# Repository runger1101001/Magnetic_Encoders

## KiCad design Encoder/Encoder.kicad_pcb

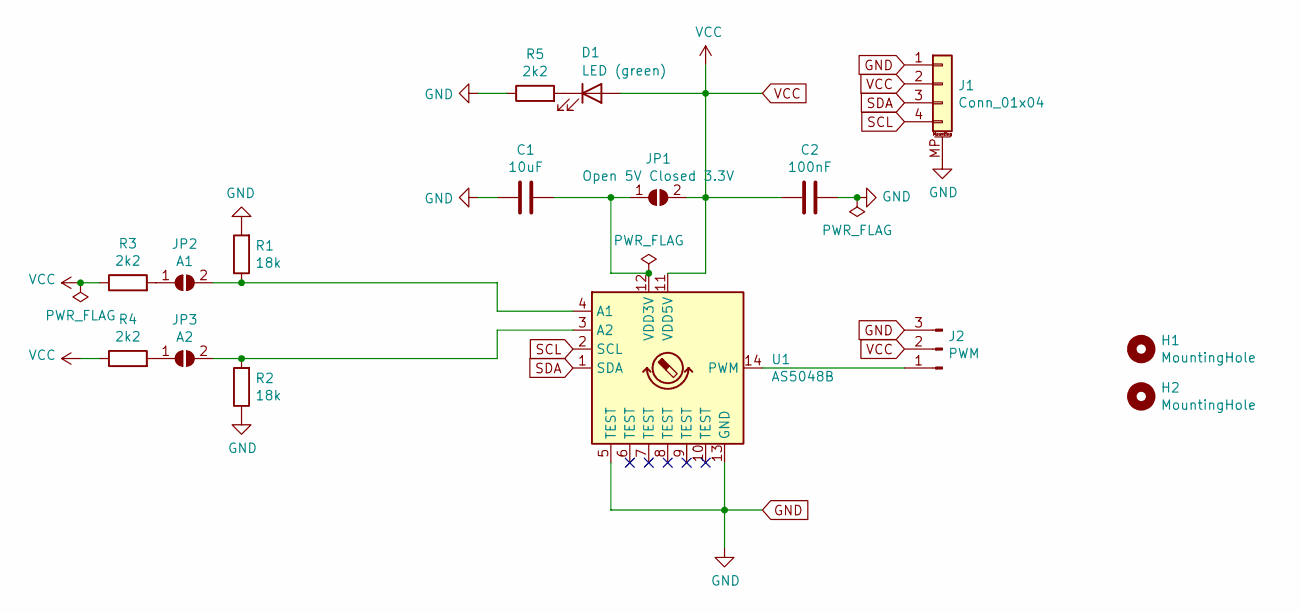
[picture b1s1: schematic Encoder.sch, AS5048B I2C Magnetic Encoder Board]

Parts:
C1: 10uF; C_0402_1005Metric; Part GRM155R60J106ME15D
C2: 100nF; C_0402_1005Metric; Part 04026D104KAT2A
D1: LED (green); LED_0402_1005Metric; Part 150040VS73240
H1, H2: MountingHole; MountingHole_2.2mm_M2
J1: Conn_01x04; JST_SH_SM04B-SRSS-TB_1x04-1MP_P1.00mm_Horizontal; Manufacturer Part # SH_SM04B-SRSS-TB
J2: PWM; PinHeader_1x03_P2.54mm_Vertical
JP1: Open 5V Closed 3.3V; SolderJumper-2_P1.3mm_Open_TrianglePad1.0x1.5mm
JP2: A1; SolderJumper-2_P1.3mm_Open_TrianglePad1.0x1.5mm
JP3: A2; SolderJumper-2_P1.3mm_Open_TrianglePad1.0x1.5mm
R1, R2: 18k; R_0402_1005Metric
R3, R4, R5: 2k2; R_0402_1005Metric; Part Generic
U1: AS5048B; TSSOP-14_4.4x5mm_P0.65mm; Part AS5048B

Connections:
GND: C1.2, C2.1, J1.1, J1.MP (MountPin), J2.3, R1.2, R2.1, R5.1, U1.5 (TEST), U1.13 (GND)
unnamed: C1.1, JP1.1 (A), U1.12 (VDD3V)
unnamed: D1.1 (K), R5.2
unnamed: J2.1, U1.14 (PWM)
unnamed: JP2.1 (A), R3.2
unnamed: JP2.2 (B), R1.1, U1.4 (A1)
unnamed: JP3.1 (A), R4.2
unnamed: JP3.2 (B), R2.2, U1.3 (A2)
SCL: J1.4, U1.2 (SCL)
SDA: J1.3, U1.1 (SDA)
VCC: C2.2, D1.2 (A), J1.2, J2.2, JP1.2 (B), R3.1, R4.1, U1.11 (VDD5V)

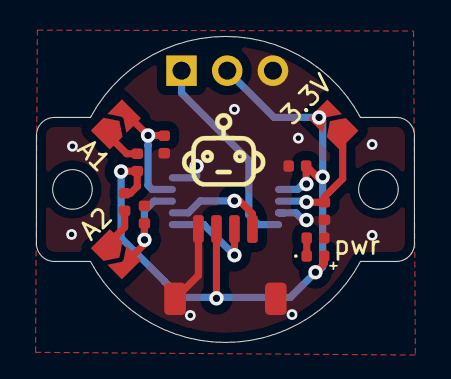
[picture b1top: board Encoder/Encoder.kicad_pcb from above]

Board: 2 copper layers, 21.0 x 17.0 mm, 16 parts (1 on the bottom side), 11 nets.

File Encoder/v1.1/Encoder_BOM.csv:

Item #,Ref Des,Qty,Manufacturer,Mfg Part #, Description / Value,Package,Type,Your Instructions / Notes
1,C1,1,Generic,Generic,10µF 6.3V Ceramic,0402,SMD,Generic
2,C2,1,Generic,Generic,100nF 6.3V Ceramic,0402,SMD,Generic
3,D1,1,Generic,e.g.: SML-P13PT,LED Green (λ 560nm)  Vf 2.1V @20mA,0402,SMD,"Generic, e.g. https://eu.mouser.com/datasheet/2/348/sml-p1-e-1874493.pdf"
4,J1,1,JST,SM04B-SRSS-TB,Conn_01x04,SM04B-SRSS-TB,SMD,http://www.jst-mfg.com/product/pdf/eng/eSH.pdf?5f7229e446c85
5,"R1,R2",2,Generic,Generic,18kΩ 1/16W 2%,0402,SMD,Generic
6,"R3,R4,R5",3,Generic,Generic,2.2kΩ 1/16W 2%,0402,SMD,Generic
7,U1,1,AMS,AS5048B,AS5048B,TSSOP-14,SMD,https://ams.com/documents/20143/36005/AS5048_DS000298_4-00.pdf

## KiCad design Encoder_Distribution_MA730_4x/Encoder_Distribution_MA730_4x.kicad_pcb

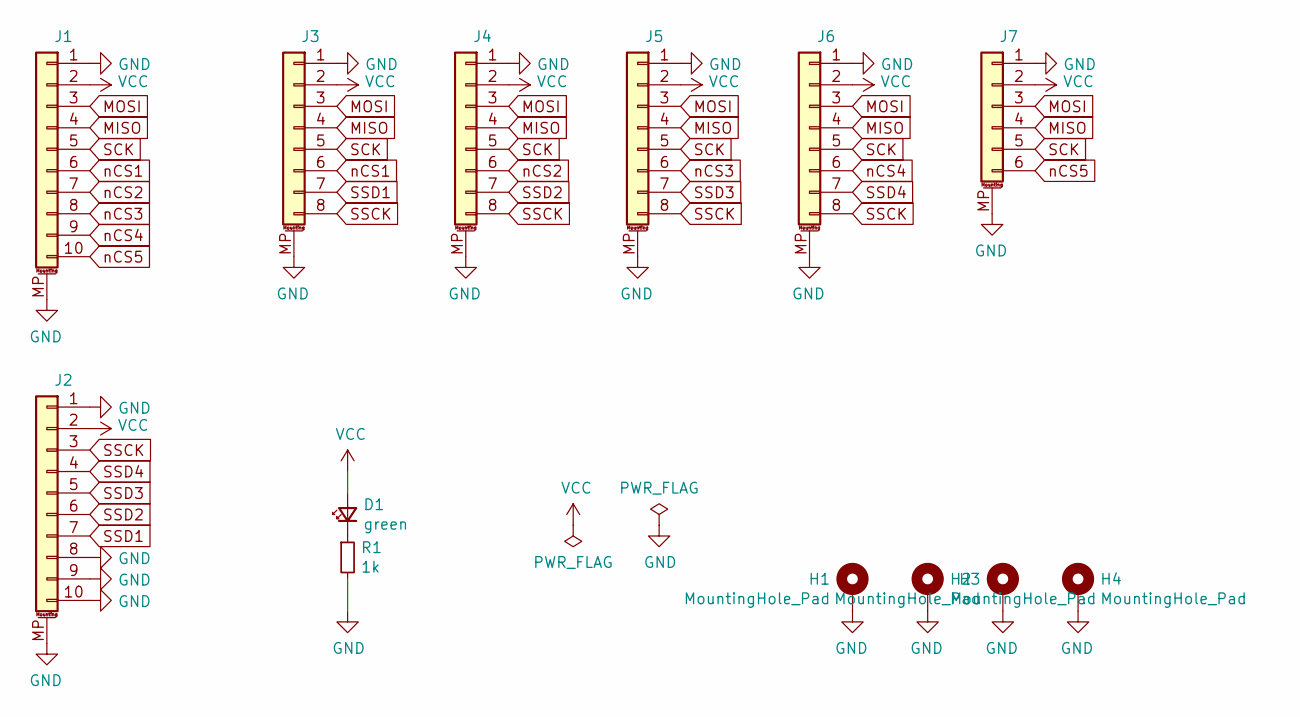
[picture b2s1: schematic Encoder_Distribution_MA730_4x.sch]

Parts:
D1: green; LED_0402_1005Metric; Part 150040VS73240
H1, H2, H3, H4: MountingHole_Pad; MountingHole_2.2mm_M2_ISO7380_Pad
J1, J2: Conn_01x10_MountingPin; JST_SH_SM10B-SRSS-TB_1x10-1MP_P1.00mm_Horizontal; Part SH_SM10B-SRSS-TB_1x10
J3, J4, J5, J6: Conn_01x08_MountingPin; JST_SH_BM08B-SRSS-TB_1x08-1MP_P1.00mm_Vertical; Part SH_BM06B-SRSS-TB_1x08
J7: Conn_01x06_MountingPin; JST_SH_BM06B-SRSS-TB_1x06-1MP_P1.00mm_Vertical; Part SH_BM06B-SRSS-TB_1x06
R1: 1k; R_0402_1005Metric

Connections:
GND: H1.1, H2.1, H3.1, H4.1, J1.1, J1.MP (MountPin), J2.1, J2.8, J2.9, J2.10, J2.MP (MountPin), J3.1, J3.MP (MountPin), J4.1, J4.MP (MountPin), J5.1, J5.MP (MountPin), J6.1, J6.MP (MountPin), J7.1, J7.MP (MountPin), R1.2
MISO: J1.4, J3.4, J4.4, J5.4, J6.4, J7.4
MOSI: J1.3, J3.3, J4.3, J5.3, J6.3, J7.3
unnamed: D1.1 (K), R1.1
SCK: J1.5, J3.5, J4.5, J5.5, J6.5, J7.5
SSCK: J2.3, J3.8, J4.8, J5.8, J6.8
SSD1: J2.7, J3.7
SSD2: J2.6, J4.7
SSD3: J2.5, J5.7
SSD4: J2.4, J6.7
VCC: D1.2 (A), J1.2, J2.2, J3.2, J4.2, J5.2, J6.2, J7.2
nCS1: J1.6, J3.6
nCS2: J1.7, J4.6
nCS3: J1.8, J5.6
nCS4: J1.9, J6.6
nCS5: J1.10, J7.6

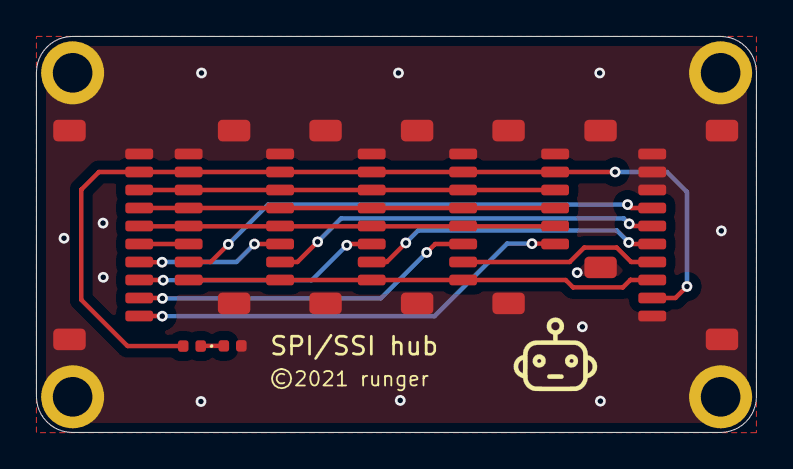
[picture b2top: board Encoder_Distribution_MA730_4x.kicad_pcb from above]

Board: 2 copper layers, 40.0 x 22.0 mm, 13 parts (0 on the bottom side), 16 nets.

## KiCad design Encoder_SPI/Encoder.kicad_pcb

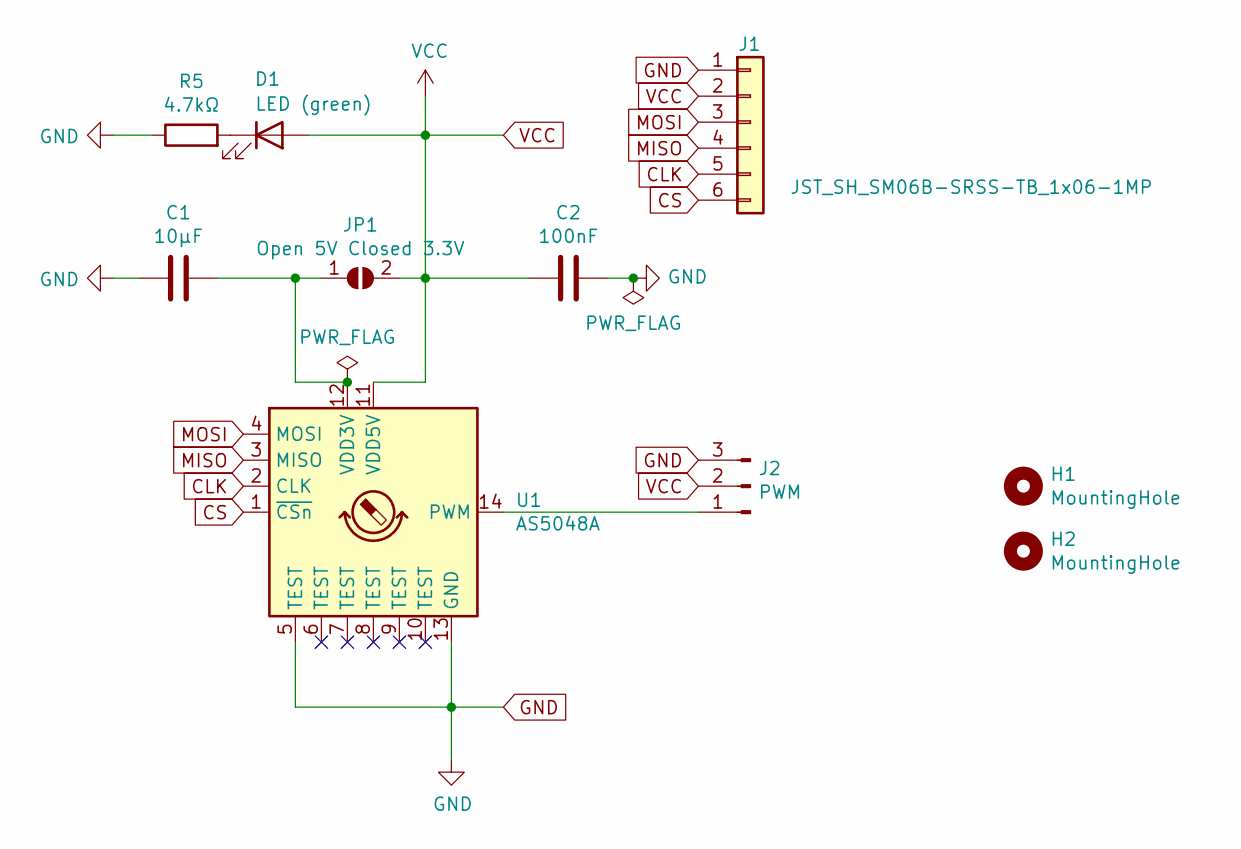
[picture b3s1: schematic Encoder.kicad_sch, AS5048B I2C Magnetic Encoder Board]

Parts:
C1: 10µF; C_0402_1005Metric
C2: 100nF; C_0402_1005Metric
D1: LED (green); LED_0402_1005Metric
H1, H2: MountingHole; MountingHole_2.2mm_M2
J1: JST_SH_SM06B-SRSS-TB_1x06-1MP; JST_SH_SM06B-SRSS-TB_1x06-1MP_P1.00mm_Horizontal; Manufacturer Part # JST_SH_SM06B-SRSS-TB_1x06-1MP
J2: PWM; PinHeader_1x03_P2.54mm_Vertical
JP1: Open 5V Closed 3.3V; SolderJumper-2_P1.3mm_Bridged_RoundedPad1.0x1.5mm
R5: 4.7kΩ; R_0402_1005Metric
U1: AS5048A; TSSOP-14_4.4x5mm_P0.65mm; Part AS5048A

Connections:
CLK: J1.5, U1.2 (CLK)
CS: J1.6, U1.1 (~CSn)
GND: C1.2, C2.1, J1.1, J2.3, R5.1, U1.5 (TEST), U1.13 (GND)
MISO: J1.4, U1.3 (MISO)
MOSI: J1.3, U1.4 (MOSI)
unnamed: C1.1, JP1.1 (A), U1.12 (VDD3V)
unnamed: D1.1 (K), R5.2
unnamed: J2.1, U1.14 (PWM)
VCC: C2.2, D1.2 (A), J1.2, J2.2, JP1.2 (B), U1.11 (VDD5V)

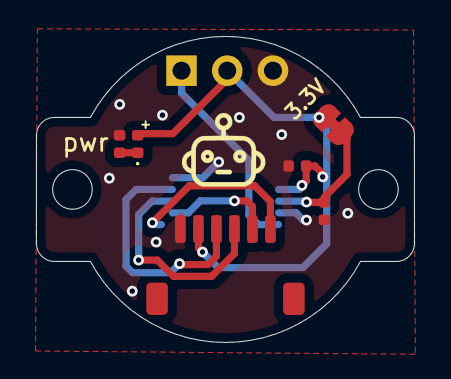
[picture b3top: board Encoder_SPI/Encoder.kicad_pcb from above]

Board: 2 copper layers, 21.0 x 17.0 mm, 10 parts (1 on the bottom side), 9 nets.

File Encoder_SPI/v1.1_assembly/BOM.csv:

Item #,Ref Des,Qty,Manufacturer,Mfg Part #, Description / Value,Package,Type,Your Instructions / Notes
1,U1,1,AMS,AS5048A,AS5048A,TSSOP-14_4.4x5mm_P0.65mm,SMD,
2,J1,1,JST,JST_SH_SM06B-SRSS-TB_1x06-1MP,JST SH 1.0mm 6-pin horizontal socket,JST_SH_SM06B-SRSS-TB_1x06-1MP_P1.00mm_Horizontal,SMD,
7,R5,1,Generic,Generic,4k7,R_0402_1005Metric,SMD,
8,D1,1,ROHM,SML-P12MTT86,Green LED,LED_0402_1005Metric,SMD,"Please choose inexpensive green LED, for example ROHM SML-P13FTT86R"
9,C2,1,Samsung,CL05B104KQ5NNNC,100nF 6.3V Ceramic,C_0402_1005Metric,SMD,
10,C1,1,Murata,ZRB15XR61A106ME01D,10uF 10V Ceramic,C_0402_1005Metric,SMD,

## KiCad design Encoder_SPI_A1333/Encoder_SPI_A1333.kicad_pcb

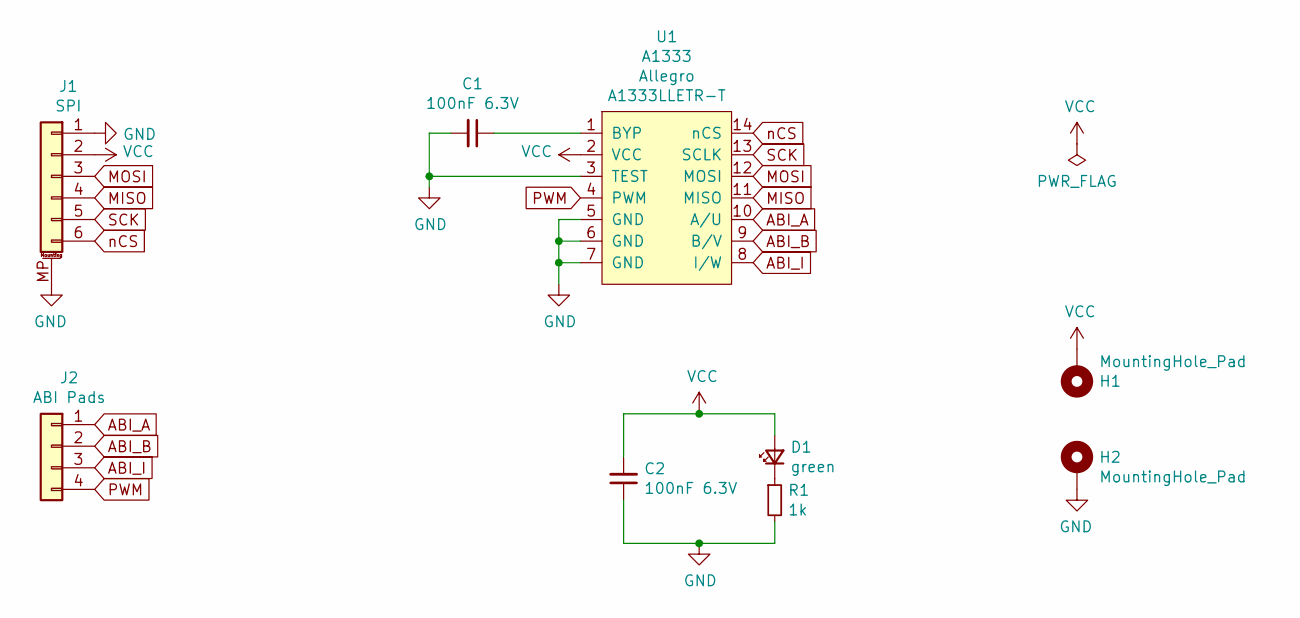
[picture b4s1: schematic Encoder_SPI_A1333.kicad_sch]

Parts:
C1, C2: 100nF 6.3V; C_0402_1005Metric; Part Generic
D1: green; LED_0402_1005Metric; Part 150040VS73240
H1, H2: MountingHole_Pad; MountingHole_2.2mm_M2_ISO7380_Pad
J1: Conn_01x06_MountingPin; JST_SH_SM06B-SRSS-TB_1x06-1MP_P1.00mm_Horizontal; Part SH_SM06B-SRSS-TB_1x06-1MP_P1.00mm_Horiz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
J2: Castellations_ABI; PinHeader_1x04_P2.54mm_Vertical
R1: 1k; R_0402_1005Metric; Part Generic 1k Resistor
U1: A1333; TSSOP-14_4.4x5mm_P0.65mm; Part A1333LLETR-T

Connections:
ABI_A: J2.1, U1.10 (A/U)
ABI_B: J2.2, U1.9 (B/V)
ABI_I: J2.3, U1.8 (I/W)
GND: C1.2, C2.1, H2.1, J1.1, J1.MP (MountPin), R1.2, U1.3 (TEST), U1.5 (GND), U1.6 (GND), U1.7 (GND)
MISO: J1.4, U1.11 (MISO)
MOSI: J1.3, U1.12 (MOSI)
unnamed: C1.1, U1.1 (BYP)
unnamed: D1.1 (K), R1.1
PWM: J2.4, U1.4 (PWM)
SCK: J1.5, U1.13 (SCLK)
VCC: C2.2, D1.2 (A), H1.1, J1.2, U1.2 (VCC)
nCS: J1.6, U1.14 (nCS)

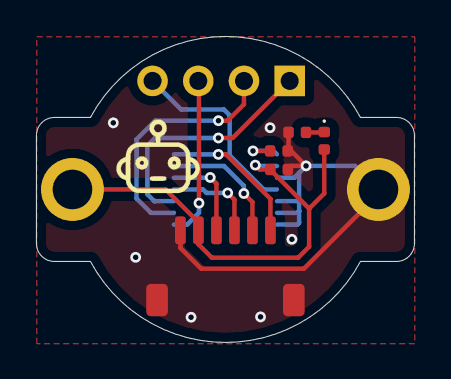
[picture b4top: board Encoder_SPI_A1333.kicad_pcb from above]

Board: 2 copper layers, 21.0 x 17.0 mm, 9 parts (1 on the bottom side), 12 nets.

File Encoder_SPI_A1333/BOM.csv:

"Item","Ref Des","Qty","Manufacturer","Mfg Part #","Description / Value","Package","Type","Your Instructions / Notes"
"1","C1,C2","2","Generic","Generic","100nF 6.3V","C_0402_1005Metric","?","; Unpolarized capacitor; "
"2","D1","1","Wurth","150040VS73240","green","LED_0402_1005Metric","?","; Light emitting diode; "
"3","H2,H1","2","","Mounting Hole with connection","MountingHole_Pad","MountingHole_2.2mm_M2_ISO7380_Pad","?","; Mounting Hole with connection; "
"4","J1","1","JST","SH_SM06B-SRSS-TB_1x06-1MP_P1.00mm_Horizontal","Conn_01x06_MountingPin","JST_SH_SM06B-SRSS-TB_1x06-1MP_P1.00mm_Horizontal","?","; Generic connectable mounting pin connector, single row, 01x06, script generated (kicad-library-utils/schlib/autogen/connector/); "
"5","J2","1","","Generic connector, single row, 01x04, script generated (kicad-library-utils/schlib/autogen/connector/)","Castellations_ABI","PinHeader_1x04_P2.54mm_Vertical","?","; Generic connector, single row, 01x04, script generated (kicad-library-utils/schlib/autogen/connector/); "
"6","R1","1","Generic","Generic 1k Resistor","1k","R_0402_1005Metric","?","; Resistor; "
"7","U1","1","Allegro","A1333LLETR-T","A1333","TSSOP-14_4.4x5mm_P0.65mm","?","; Precision, High Speed, Hall-Effect Angle Sensor IC with Integrated Diagnostics for Safety-Critical Applications, 3.3V; "

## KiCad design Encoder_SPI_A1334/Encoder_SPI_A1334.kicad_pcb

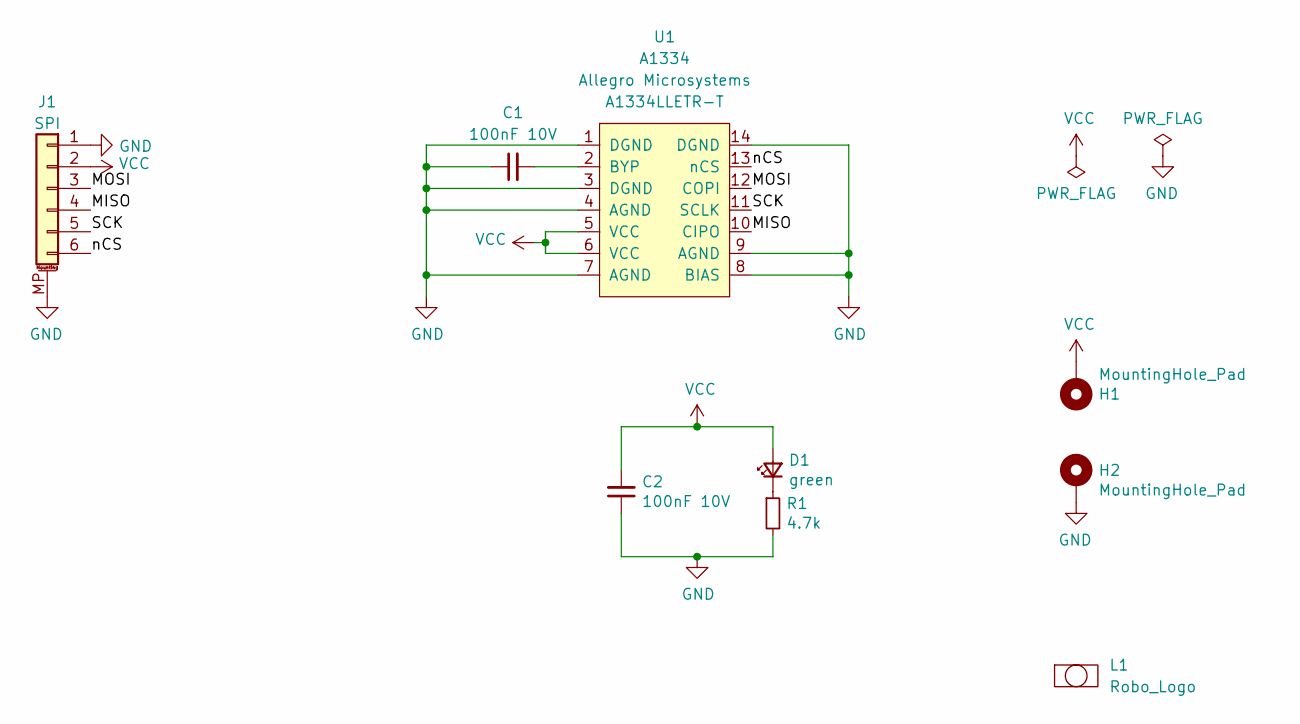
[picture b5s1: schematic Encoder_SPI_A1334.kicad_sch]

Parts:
C1, C2: 100nF 10V; C_0402_1005Metric; Part GRM155R71A104KA01J
D1: green; LED_0402_1005Metric; Part 150040VS73240
H1, H2: MountingHole_Pad; MountingHole_2.2mm_M2_ISO7380_Pad
J1: Conn_01x06_MountingPin; JST_SH_SM06B-SRSS-TB_1x06-1MP_P1.00mm_Horizontal; Part SCT-WR-S-06P
L1: Robo_Logo; Robo_logo2
R1: 4.7k; R_0402_1005Metric; Part Generic 1k Resistor
U1: A1334; TSSOP-14_4.4x5mm_P0.65mm; Part A1334LLETR-T

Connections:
/MISO: J1.4, U1.10 (CIPO)
/MOSI: J1.3, U1.12 (COPI)
/SCK: J1.5, U1.11 (SCLK)
/nCS: J1.6, U1.13 (nCS)
GND: C1.1, C2.1, H2.1, J1.1, J1.MP (MountPin), R1.2, U1.1 (DGND), U1.3 (DGND), U1.4 (AGND), U1.7 (AGND), U1.8 (BIAS), U1.9 (AGND), U1.14 (DGND)
unnamed: C1.2, U1.2 (BYP)
unnamed: D1.1 (K), R1.1
VCC: C2.2, D1.2 (A), H1.1, J1.2, U1.5 (VCC), U1.6 (VCC)

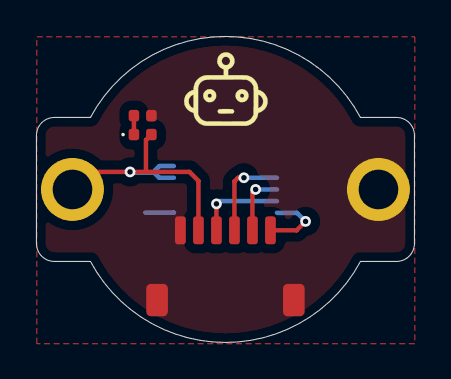
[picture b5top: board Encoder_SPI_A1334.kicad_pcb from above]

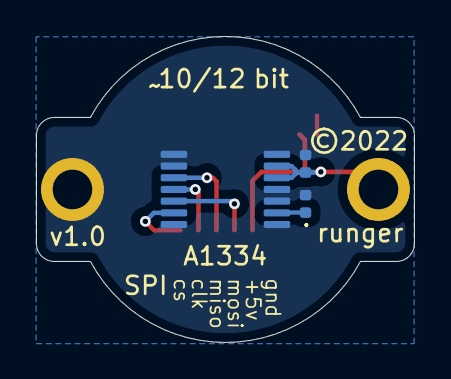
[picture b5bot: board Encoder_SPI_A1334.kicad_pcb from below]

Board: 2 copper layers, 21.0 x 17.0 mm, 9 parts (3 on the bottom side), 8 nets.

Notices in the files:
Encoder/Encoder.kicad_pcb:
©2021
Encoder_Distribution_MA730_4x/Encoder_Distribution_MA730_4x.kicad_pcb:
©2021 runger
Encoder_SPI/Encoder.kicad_pcb:
©2022
